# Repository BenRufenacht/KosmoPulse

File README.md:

# KosmoPulse
 Music Thing Modular Pulse Expander for the Turing Machine converted to Kosmo Format

[Schematic](https://github.com/TomWhitwell/Turing-Pulse-Expander/blob/master/Collateral/pulses_rev2_schematic.pdf)

Status:   
June 2022 - Boards have not been manufactured or tested

License:  
[CC-BY-SA](https://creativecommons.org/licenses/by-sa/3.0/)

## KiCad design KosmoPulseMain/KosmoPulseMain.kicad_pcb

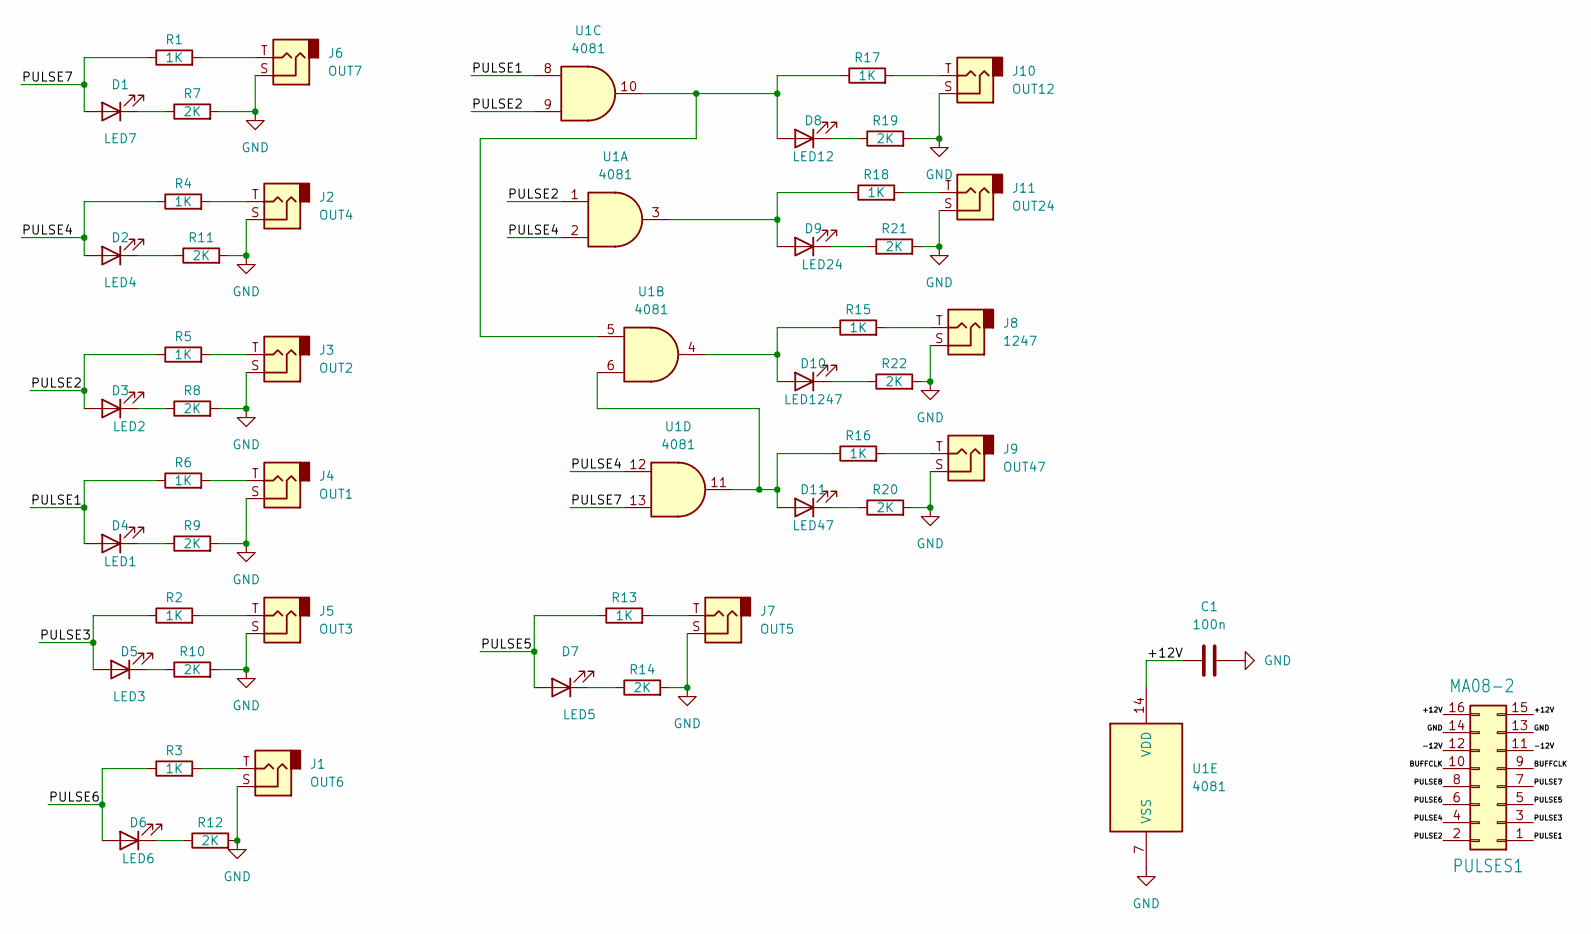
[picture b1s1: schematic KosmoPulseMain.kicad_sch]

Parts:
C1: 100n; C_Rect_L7.2mm_W2.5mm_P5.00mm_FKS2_FKP2_MKS2_MKP2
D1: LED7; LED_D5.0mm
D2: LED4; LED_D5.0mm
D3: LED2; LED_D5.0mm
D4: LED1; LED_D5.0mm
D5: LED3; LED_D5.0mm
D6: LED6; LED_D5.0mm
D7: LED5; LED_D5.0mm
D8: LED12; LED_D5.0mm
D9: LED24; LED_D5.0mm
D10: LED1247; LED_D5.0mm
D11: LED47; LED_D5.0mm
J1: OUT6; Jack_6.35mm_PJ_629HAN
J2: OUT4; Jack_6.35mm_PJ_629HAN
J3: OUT2; Jack_6.35mm_PJ_629HAN
J4: OUT1; Jack_6.35mm_PJ_629HAN
J5: OUT3; Jack_6.35mm_PJ_629HAN
J6: OUT7; Jack_6.35mm_PJ_629HAN
J7: OUT5; Jack_6.35mm_PJ_629HAN
J8: 1247; Jack_6.35mm_PJ_629HAN
J9: OUT47; Jack_6.35mm_PJ_629HAN
J10: OUT12; Jack_6.35mm_PJ_629HAN
J11: OUT24; Jack_6.35mm_PJ_629HAN
PULSES1: MA08-2; IDC-Header_2x08_P2.54mm_Vertical
R1, R2, R3, R4, R5, R6, R13, R15, R16, R17, R18: 1K; R_Axial_DIN0207_L6.3mm_D2.5mm_P10.16mm_Horizontal
R7, R8, R9, R10, R11, R12, R14, R19, R20, R21, R22: 2K; R_Axial_DIN0207_L6.3mm_D2.5mm_P10.16mm_Horizontal
U1: 4081; DIP-14_W7.62mm_Socket_LongPads

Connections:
/+12V: C1.1, PULSES1.15, PULSES1.16, U1.14 (VDD)
/-12V: PULSES1.11, PULSES1.12
/BUFFCLK: PULSES1.9, PULSES1.10
/PULSE1: D4.2 (A), PULSES1.1, R6.1, U1.8
/PULSE2: D3.2 (A), PULSES1.2, R5.1, U1.1, U1.9
/PULSE3: D5.2 (A), PULSES1.3, R2.1
/PULSE4: D2.2 (A), PULSES1.4, R4.1, U1.2, U1.12
/PULSE5: D7.2 (A), PULSES1.5, R13.1
/PULSE6: D6.2 (A), PULSES1.6, R3.1
/PULSE7: D1.2 (A), PULSES1.7, R1.1, U1.13
/PULSE8: PULSES1.8
unnamed: D1.1 (K), R7.1
unnamed: D2.1 (K), R11.1
unnamed: D3.1 (K), R8.1
unnamed: D4.1 (K), R9.1
unnamed: D5.1 (K), R10.1
unnamed: D6.1 (K), R12.1
unnamed: D7.1 (K), R14.1
unnamed: D8.1 (K), R19.1
unnamed: D8.2 (A), R17.1, U1.5, U1.10
unnamed: D9.1 (K), R21.1
unnamed: D9.2 (A), R18.1, U1.3
unnamed: D10.1 (K), R22.1
unnamed: D10.2 (A), R15.1, U1.4
unnamed: D11.1 (K), R20.1
unnamed: D11.2 (A), R16.1, U1.6, U1.11
unnamed: J1.T, R3.2
unnamed: J2.T, R4.2
unnamed: J3.T, R5.2
unnamed: J4.T, R6.2
unnamed: J5.T, R2.2
unnamed: J6.T, R1.2
unnamed: J7.T, R13.2
unnamed: J8.T, R15.2
unnamed: J9.T, R16.2
unnamed: J10.T, R17.2
unnamed: J11.T, R18.2

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
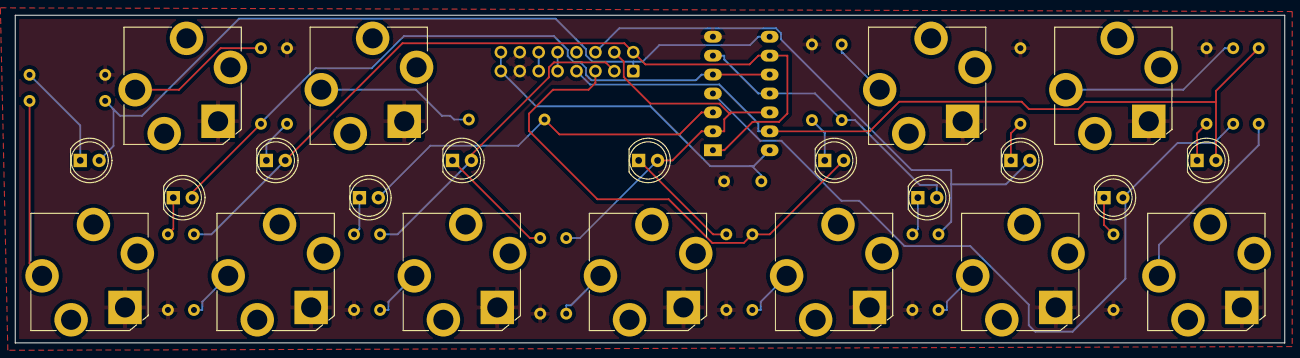
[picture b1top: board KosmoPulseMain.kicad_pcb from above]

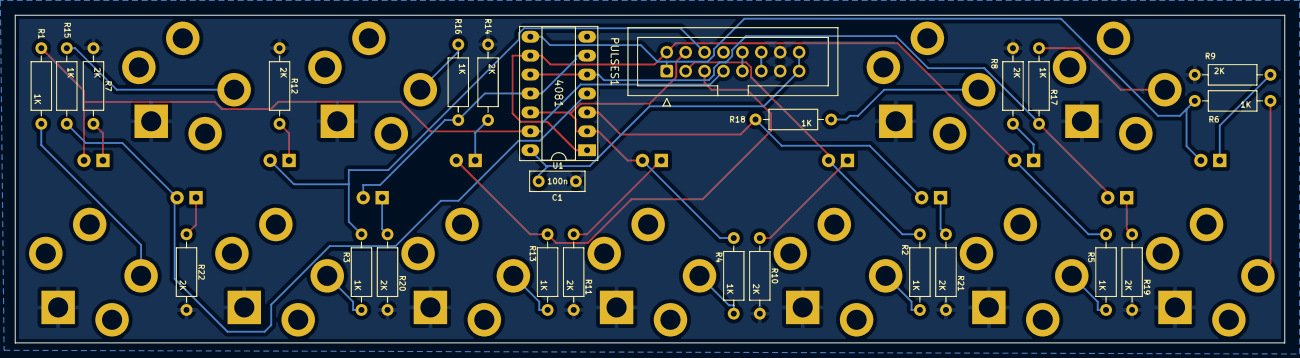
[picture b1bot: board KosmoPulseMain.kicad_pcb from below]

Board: 2 copper layers, 170.5 x 44.0 mm, 47 parts (25 on the bottom side), 37 nets.

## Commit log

2022-06-10 Manufacturing Update
2022-07-11 Fix jack alignment on panel
2022-07-31 Added GND to BIT 6
